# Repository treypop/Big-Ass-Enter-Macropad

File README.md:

# Big-Ass-Enter-Macropad

  This is a one key macropad that uses the big ass enter style of enter key. It uses the steelseries 6gv2 version of the big ass enter key.

This project is still a work in progress.

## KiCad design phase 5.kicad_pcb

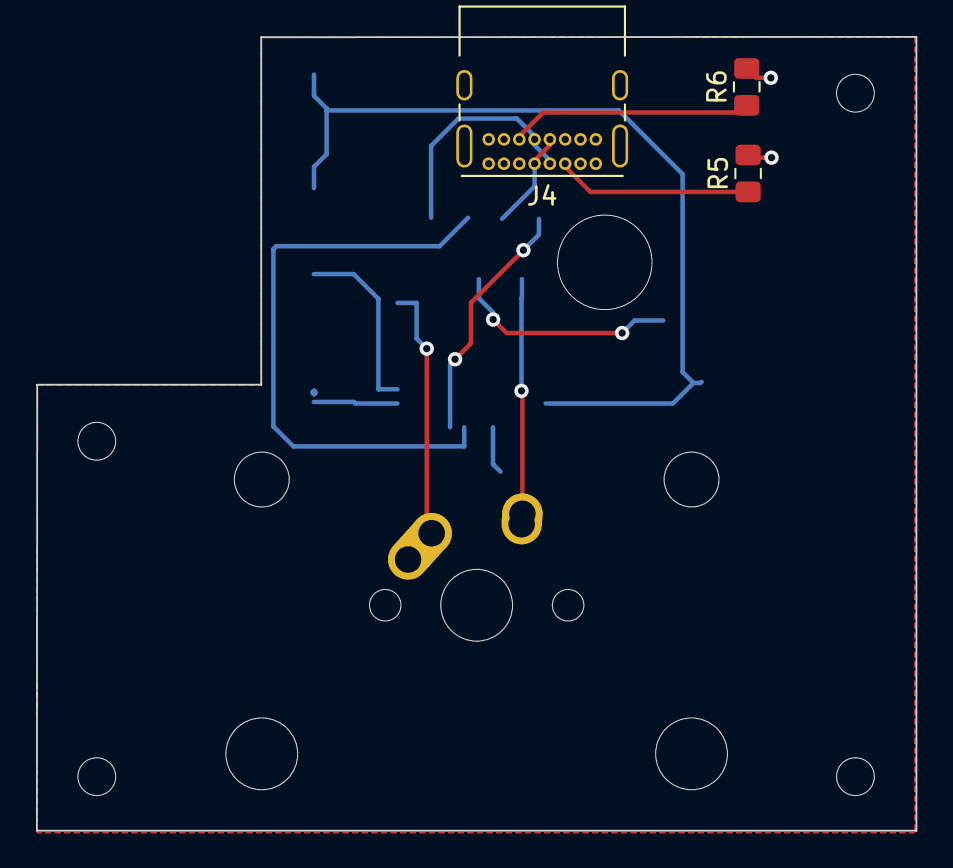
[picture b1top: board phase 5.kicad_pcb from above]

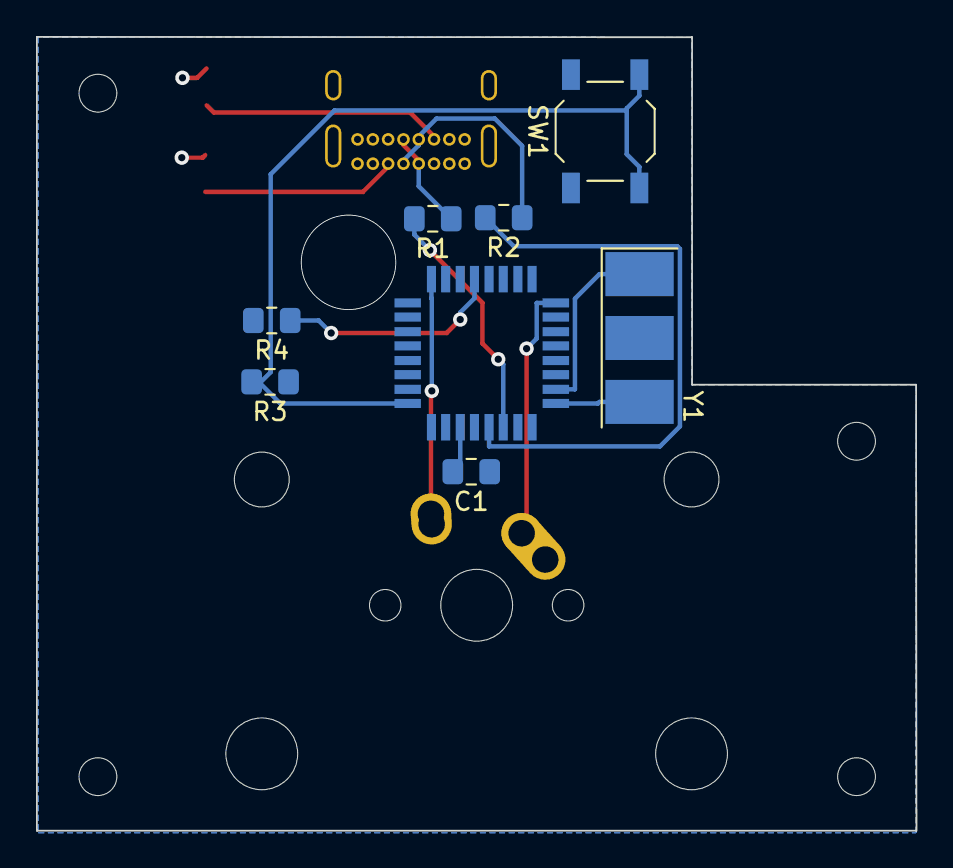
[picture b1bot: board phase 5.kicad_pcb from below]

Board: 2 copper layers, 48.9 x 44.1 mm, 12 parts (8 on the bottom side), 13 nets.

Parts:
C1: C6; C_0805_2012Metric_Pad1.15x1.40mm_HandSolder
J4: USB_C_Receptacle_USB2.0; USB_C_Receptacle_GCT_USB4085
K_BOTTOM_ENTER: KEYSW; MX-2.25U-NoLED
R1, R2: 22Ohm; R_0805_2012Metric_Pad1.15x1.40mm_HandSolder
R3, R4: 10kOhm; R_0805_2012Metric_Pad1.15x1.40mm_HandSolder
R5, R6: 5.1kohm; R_0805_2012Metric_Pad1.15x1.40mm_HandSolder
SW1: SW_PUSH; SW_SPST_TL3342
U1: ATMEGA32U2; ATMEGA16U2-AUR
Y1: Resonator; Resonator_SMD-3Pin_7.2x3.0mm_HandSoldering

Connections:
GND: C1.1, J4.A1, J4.A12, J4.B1, J4.B12, J4.S1, R4.2, R5.2, R6.2, SW1.1, U1.3, U1.28, Y1.2
unnamed: C1.2, U1.27
unnamed: J4.A5, R5.1
unnamed: J4.A6, J4.B6, R2.1
unnamed: J4.A7, J4.B7, R1.1
unnamed: J4.B5, R6.1
unnamed: R1.2, U1.30
unnamed: R2.2, U1.29
unnamed: R3.2, SW1.2, U1.24
unnamed: R4.1, U1.13
unnamed: U1.1, Y1.3
unnamed: U1.2, Y1.1
VCC: J4.A4, J4.A9, J4.B4, J4.B9, R3.1, U1.4, U1.31, U1.32

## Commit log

2020-07-02 Create filr
2020-07-02 Create 1
2020-07-02 Create blank
2020-07-14 README.md
